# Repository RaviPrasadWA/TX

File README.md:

# TX
NRF based transmitter with FHSS ( aka AFHDS )

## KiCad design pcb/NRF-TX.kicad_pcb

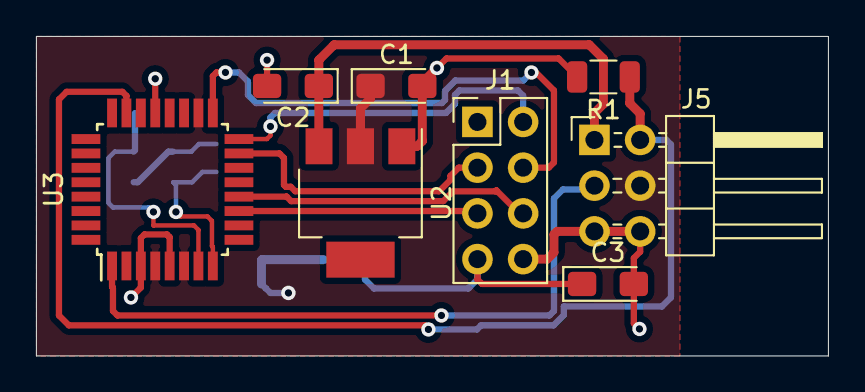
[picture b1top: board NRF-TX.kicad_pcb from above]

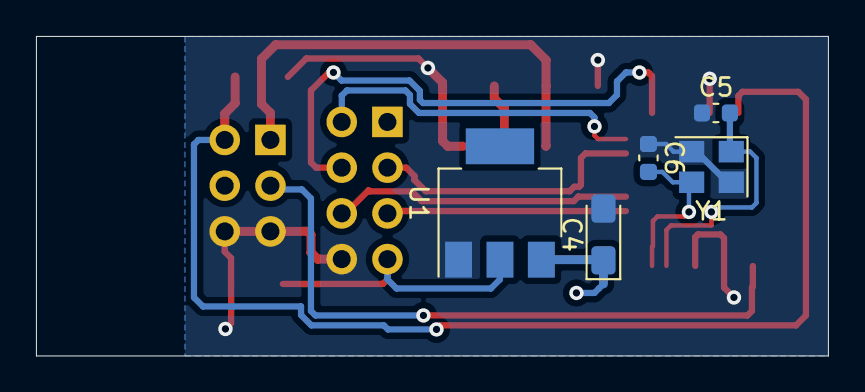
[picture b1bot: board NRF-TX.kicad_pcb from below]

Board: 2 copper layers, 44.0 x 17.8 mm, 13 parts (5 on the bottom side), 13 nets.

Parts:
C1, C2, C3, C4: 10uF; CP_EIA-3216-18_Kemet-A_Pad1.58x1.35mm_HandSolder
C5, C6: 16pF; C_0603_1608Metric
J1: Conn_02x04_Odd_Even; PinHeader_2x04_P2.54mm_Vertical
J5: Conn_02x03_Odd_Even; PinHeader_2x03_P2.54mm_Horizontal
R1: 10k; R_1206_3216Metric
U1: LM1117-3.3; SOT-223
U2: LM1117-5.0; SOT-223
U3: ATmega328-AU; TQFP-32_7x7mm_P0.8mm
Y1: Crystal; Crystal_SMD_3225-4Pin_3.2x2.5mm

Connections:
+5V: C2.1, J5.1, U2.3
GND: C1.2, C2.2, C3.2, C4.2, C5.1, C6.1, J1.8, J5.5, J5.6, R1.2, U1.1, U2.1, U3.3, U3.5, U3.21, Y1.2, Y1.4
unnamed: C1.1, C4.1, J5.4, U1.3, U2.2, U3.4, U3.6, U3.18
unnamed: C3.1, J1.7, U1.2
unnamed: C5.2, U3.7, Y1.1
unnamed: C6.2, U3.8, Y1.3
unnamed: J1.2, U3.16
unnamed: J1.3, U3.15
unnamed: J1.4, U3.17
unnamed: J1.5, U3.11
unnamed: J1.6, U3.12
unnamed: J5.2, R1.1, U3.23
unnamed: J5.3, U3.1

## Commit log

2020-10-25 added the code form the older NRF-RX TODO: add watchdog
2021-01-14 pcb base design impl TODO: add the solid layering +5v(rect) and GND
2021-01-14 added the layers
2021-01-17 added the edge cuts on the PCB
2021-02-14 added the measured PCB along with the lower case mech files TODO: upper_case
